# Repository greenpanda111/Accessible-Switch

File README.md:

# Accessible-Switch

<div align="center">

</div>

Accessible switches allow people with disabilities to interact with toys, games, or other technologies. They come in many different shapes, sizes, styles, and actuation forces. Each person has their unique switch configuration that best allows them to have maximum freedom. However, these switches can cost as low as £30 for a single, basic switch. This repository aims to improve access to a basic variety of switch for families and charities.

The switch is assembled from three 3D printed parts, a custom PCB, a [microswitch](https://uk.farnell.com/omron-electronic-components/d2fs-f-n/microswitch-plunger-spst-0-1a/dp/2402441), a [3.5mm mono jack cable](https://www.amazon.co.uk/RUNCCI-YUN-3-5mm-soldering-Repairing-Cables/dp/B0CWQN1W4J?crid=MMFTKL1YISWD&dib=eyJ2IjoiMSJ9.itFXnqrHVudY9Z76Te3JtlT01_a-7Km_P17nFm4Sf2gwNhseV51UFiYnosFNDR1xwQ9gm_AzfMkGYtUo6osAB6a1qEl-Sp-rxNtT5IVoGAxn-zgHXx88rj1oECnSUbXHlrZ6uehkS7qUX9E-YJaPP2mTWnB9Y31Y1yASitDzZAd5OjtuuSsEVc0NdKAGMeONEOkIs0AsbOu17C1xOijw-v_hRG6Owl-uLl4tAFDs8N8.JGRQKBqizKdxFqpfQaw0XqMhGhysNfbUMtKBu0fcRTM&dib_tag=se&keywords=3.5mm+mono+jack+cable+solder&qid=1748028946&sprefix=3.5mm+mono+jack+cable+solder%2Caps%2C100&sr=8-5), and three springs.

<div align="center">

</div>

# PCB
PCBs can be ordered through [JLCPCB](https://jlcpcb.com/) with default parameters. Simply download the gerbers.rar file and upload it to JLCPCB. The PCBs only require three pins soldering for the microswitch, and the two mono jack wires. Polarity of the wires does not matter, but when soldering the microswitch, the plunger should be closest to the white circle on the silkscreen. This should be accomplishable by someone with minimal soldering experience. The PCBs also have debouncing capacitor support, but these are not neccessary. A 100uA capacitor would be suitable, however.

<div align="center">

</div>

# CAD
Onshape files here: https://cad.onshape.com/documents/298bde2cf99925c17ee02d94/w/1b669208b51cf1bc021c468f/e/d7502f0e0361710259ea8cca 

<div align="center">

</div>

# Future Improvements:

- Redesign the PCB mounting in the base so that it has a snap-fit connection so screws are not needed. This would allow the base to be even slimmer
- Version 2.0 where there is no locking ring and the plunger can reach the edge of the base

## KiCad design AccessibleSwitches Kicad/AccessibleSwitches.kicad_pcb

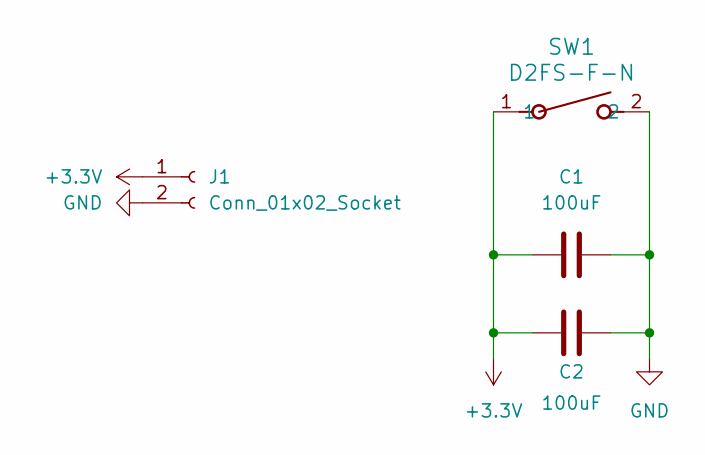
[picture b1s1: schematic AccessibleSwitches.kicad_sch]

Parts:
C1: 100uF; C_0603_1608Metric_Pad1.08x0.95mm_HandSolder
C2: 100uF; CP_Radial_D6.3mm_P2.50mm
J1: Conn_01x02_Socket; PinSocket_1x02_P2.54mm_Vertical
SW1: D2FS-F-N; SW_D2FS-F-N_OMR

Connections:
+3.3V: C1.1, C2.1, J1.1, SW1.1
GND: C1.2, C2.2, J1.2, SW1.2

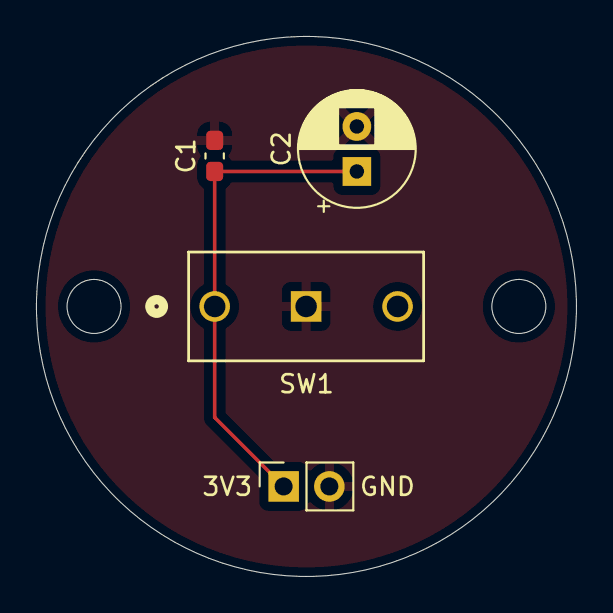
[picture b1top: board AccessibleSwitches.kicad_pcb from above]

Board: 2 copper layers, 30.0 x 30.0 mm, 4 parts (0 on the bottom side), 2 nets.

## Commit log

2025-04-04 Current Switch STLs added
2025-04-04 PCB Images
2025-04-04 CAD Image
2025-04-06 Gerbers added
2025-04-06 git ignore in effect
2025-04-06 Kicad files re-added
2025-04-06 SMD debouncing cap added
2025-04-06 Gerbers and 3D model exported
2025-04-06 Images relocated
2025-04-06 old images removed
2025-04-06 traces cleaned up
2025-04-23 Updated CAD Image
2025-05-17 Create LICENSE
2025-05-23 New images
2025-05-23 Smooth and slimmer switches
